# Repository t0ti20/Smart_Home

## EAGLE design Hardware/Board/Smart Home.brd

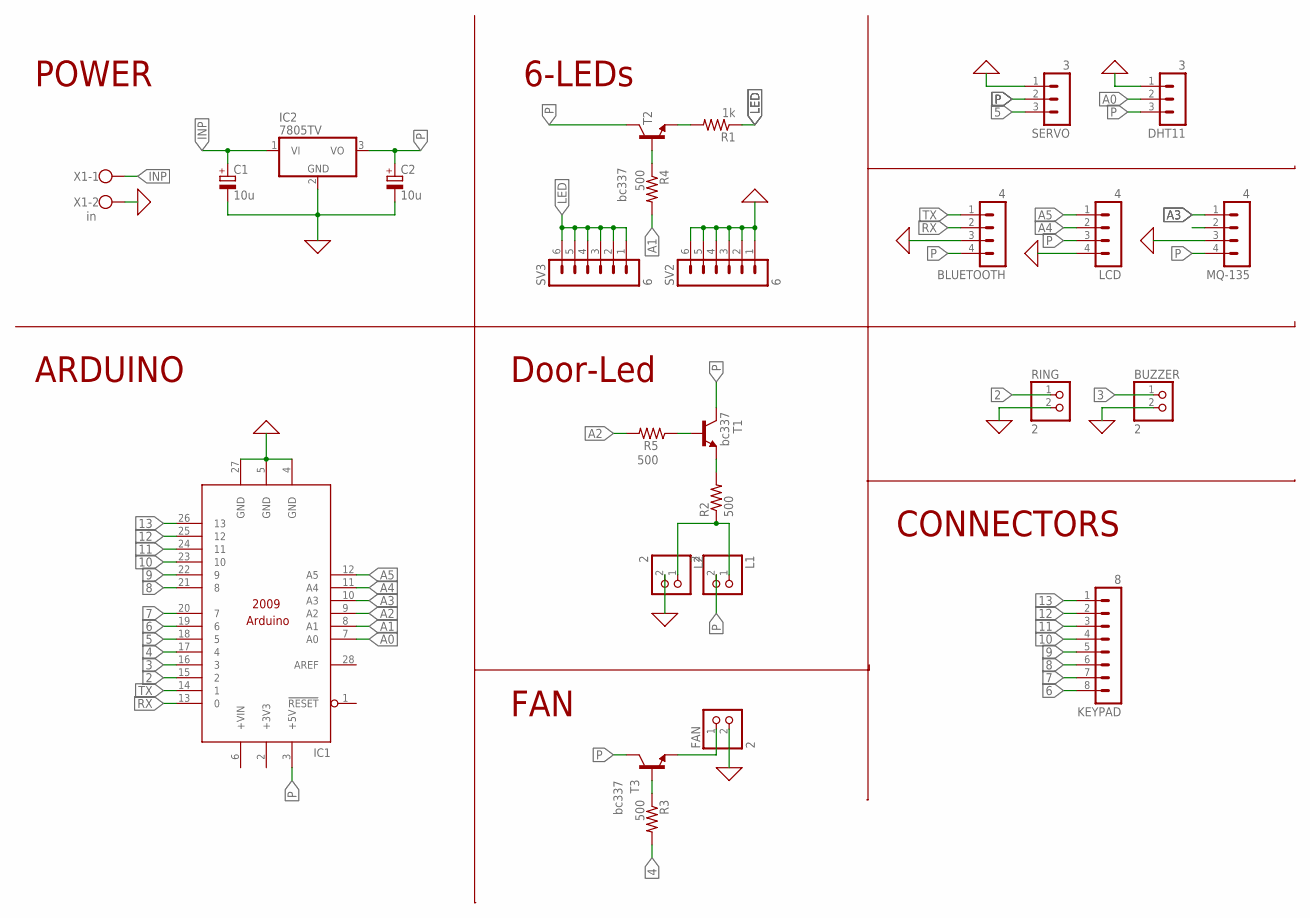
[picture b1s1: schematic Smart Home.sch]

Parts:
BLUETOOTH: 4; MA04-1
BUZZER: 2; 1X02
C1, C2: 10u; E2,5-6
DHT11: 3; MA03-1
FAN: 2; 1X02
IC1: uno; ARDUINO2009_2
IC2: 7805TV; TO220V
KEYPAD: 8; MA08-1
L1, L2: 2; 1X02
LCD: 4; MA04-1
MQ-135: 4; MA04-1
R1: 1k; 0207/10
R2, R3, R4, R5: 500; 0207/10
RING: 2; 1X02
SERVO: 3; MA03-1
SV2, SV3: 6; MA06-1
T1, T2, T3: bc337; TO92-CBE
X1: in; W237-102

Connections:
0: BLUETOOTH.3, BUZZER.2, C1.-, C2.-, DHT11.1, FAN.2, IC1.4 (GND), IC1.5 (GND), IC1.27 (GND), IC2.2 (GND), L2.2, LCD.4, MQ-135.3, RING.2, SERVO.1, SV2.1, SV2.2, SV2.3, SV2.4, SV2.5, SV2.6, X1.2
2: IC1.15 (2), RING.1
3: BUZZER.1, IC1.16 (3)
4: IC1.17 (4), R3.2
5: IC1.18 (5), SERVO.3
6: IC1.19 (6), KEYPAD.8
7: IC1.20 (7), KEYPAD.7
8: IC1.21 (8), KEYPAD.6
9: IC1.22 (9), KEYPAD.5
10: IC1.23 (10), KEYPAD.4
11: IC1.24 (11), KEYPAD.3
12: IC1.25 (12), KEYPAD.2
13: IC1.26 (13), KEYPAD.1
+3V3: IC1.2 (+3V3)
A0: DHT11.2, IC1.7 (A0)
A1: IC1.8 (A1), R4.2
A2: IC1.9 (A2), R5.2
A3: IC1.10 (A3), MQ-135.1
A4: IC1.11 (A4), LCD.2
A5: IC1.12 (A5), LCD.1
INP: C1.+, IC2.1 (VI), X1.1
L1: L1.1, L2.1, R2.1
LED: R1.1, SV3.1, SV3.2, SV3.3, SV3.4, SV3.5, SV3.6
unnamed: R1.2, T2.E
unnamed: R2.2, T1.E
unnamed: FAN.1, T3.E
unnamed: R5.1, T1.B
unnamed: R4.1, T2.B
unnamed: R3.1, T3.B
P: BLUETOOTH.4, C2.+, DHT11.3, IC1.3 (+5V), IC2.3 (VO), L1.2, LCD.3, MQ-135.4, SERVO.2, T1.C, T2.C, T3.C
RX: BLUETOOTH.2, IC1.13 (0)
TX: BLUETOOTH.1, IC1.14 (1)

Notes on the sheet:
POWER
ARDUINO
Door-Led
FAN
6-LEDs
CONNECTORS

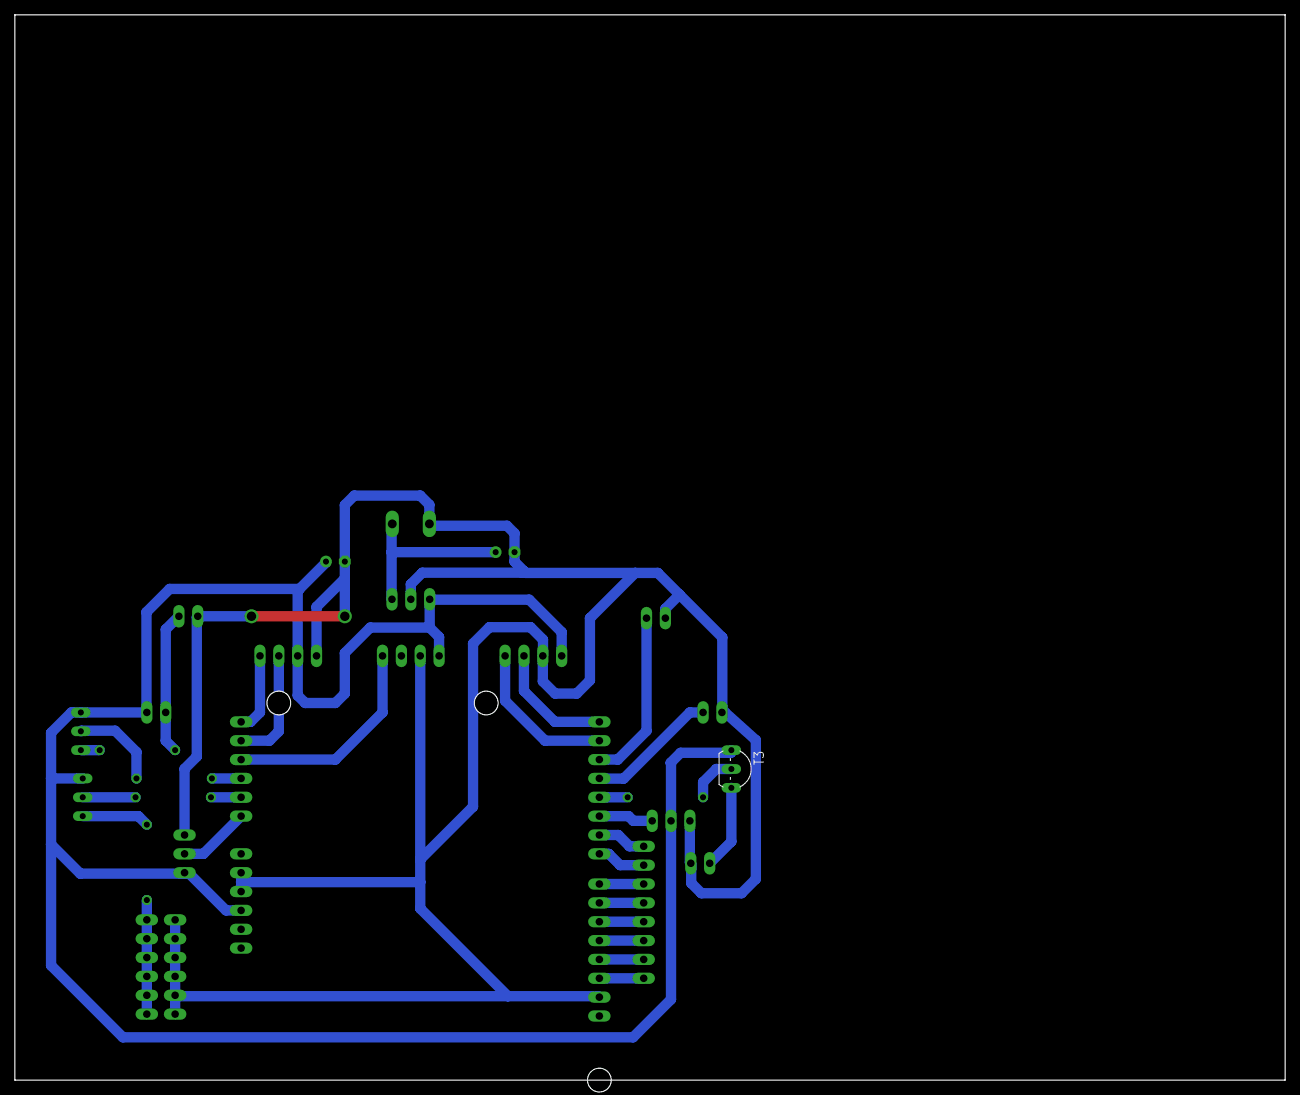
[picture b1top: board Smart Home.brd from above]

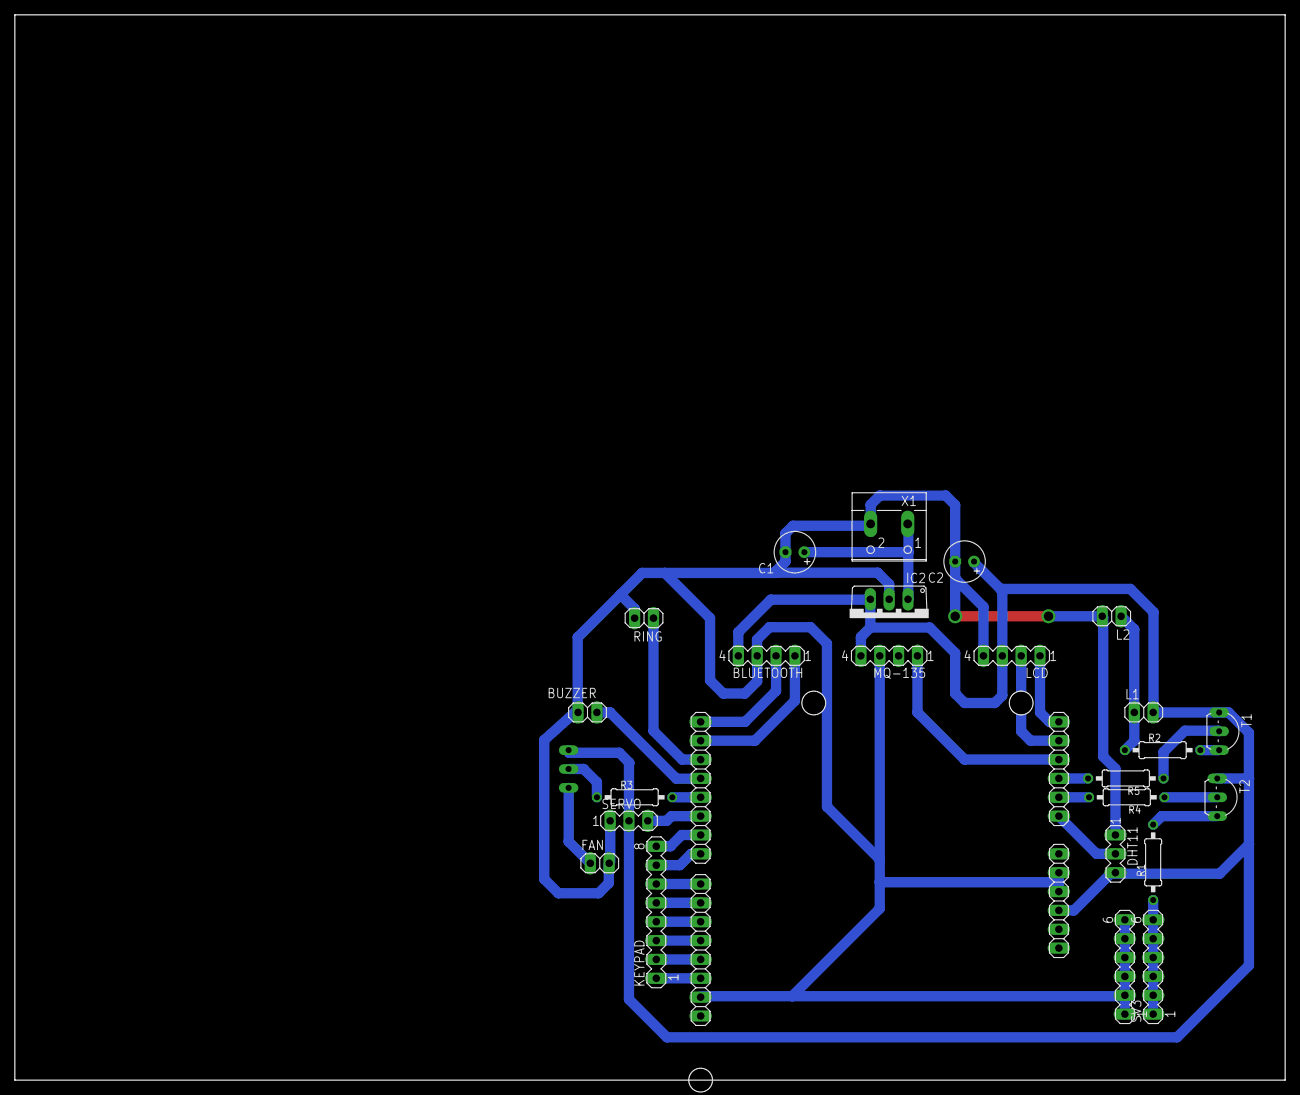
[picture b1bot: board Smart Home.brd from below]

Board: 2 copper layers, 171.1 x 143.5 mm, 26 parts (25 on the bottom side), 31 nets.

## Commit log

2022-08-20 Project Upload
